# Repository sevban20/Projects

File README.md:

# Projects
It's about Sevban Kocael's projects. New projects will add.

## ARDUINO

### Fateining Farm Project
This is Arduino Nano-based project. It has 4 buttons to control menu operations. It can work in 2 modes: Automatic feed and cleaning bed of animals like cattle, sheep, etc., another mode is that manual feed and clean. It has 2 silos to store food. Every silo has its own motor that discharges food to the mixer. Mixer prepares food. After that, the conveyor starts feeding.
It has a cleaning unit to clean the ground. In addition, it has an RTC module to keep clock info. The RTC module is powered by a CR2032 battery. DHT22 sensor was used to measure humidity and temperature.To keep fresh air in the barn were used fans that control by temperature.The board has 2 power inputs, 5V, and 12V. 6 pieces of N-channel MOSFETs have been used to power the motors.

## ESP

### Home Automation Board
This is ESP8266 based project. It can control 4 pcs relays. Every relay also has an LED display to show work situations. To detect light density it has a photocell. To measure temperature and humidity to placed DHT22 sensor. It can power up to 5V-36V. The power unit of the board is based on LM2596S. It is going to connect the firebase real-time database so it can control by mobile application or any remote-controllable app.

## LED Dimmer
It is a led dimmer using LM555. There are one INPUT and one OUTPUT. It works with 12V. The brightness is adjustable with a 50K potentiometer. The maximum current is 3A.To control led used TO-220 package N channel MOSFET-IRFZ44N-.

## Web Scraping
### Get Jobs
This is a search job from timesjob.com. A user defines keyword and other options, the script search jobs from the website and shows all of them to the user. The input choices are Keyword, Number of pages, and location experience. If the user wants to save results, there is an option to save JSON format. <br />
Keyword(Required): Jobs keywords <br />
Number of Pages(Optional): How many pages will list <br />
Location(Optional): Job's location <br />
Experience(Optional): About Years <br />
### Get Last Topic
This script is working for that when the new topic opens the donanimhaber sicak firsatlar, the script gets the topic immediately. The user can see the last opened topic. If a day passed the topic's opened date the topic automatically will delete.

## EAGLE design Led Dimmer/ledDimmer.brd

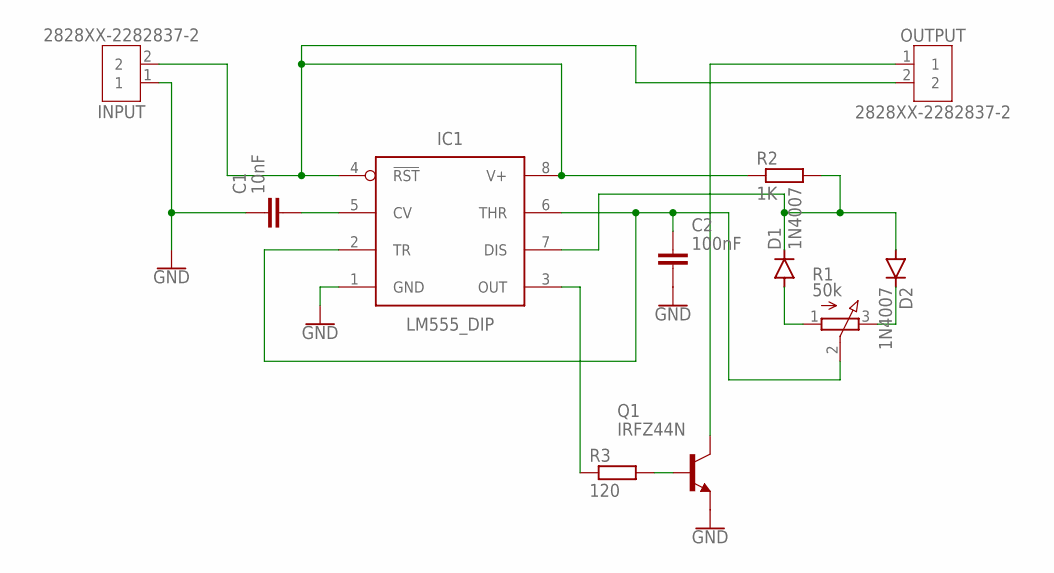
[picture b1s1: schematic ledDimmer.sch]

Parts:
C1: 10nF; CAPC1005X60
C2: 100nF; CAPC1005X60
D1, D2: 1N4007; DO-214AC
IC1: LM555_DIP; DIP826W53P254L959H508Q8B
INPUT: 2828XX-2282837-2; TERMBLK_508-2N
OUTPUT: 2828XX-2282837-2; TERMBLK_508-2N
Q1: IRFZ44N; TO220
R1: 50k; 3RP/1610N
R2: 1K; R0402
R3: 120; R0402

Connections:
GND: C1.1, C2.2, IC1.1 (GND), INPUT.1, Q1.3 (E)
unnamed: C1.2, IC1.5 (CV)
unnamed: D1.C, D2.A, IC1.7 (DIS), R2.2
unnamed: D1.A, R1.1 (A)
unnamed: D2.C, R1.3 (E)
unnamed: IC1.4 (!RST), IC1.8 (V+), INPUT.2, OUTPUT.2, R2.1
unnamed: OUTPUT.1, Q1.2 (C)
unnamed: C2.1, IC1.2 (TR), IC1.6 (THR), R1.2 (S)
unnamed: IC1.3 (OUT), R3.1
unnamed: Q1.1 (B), R3.2

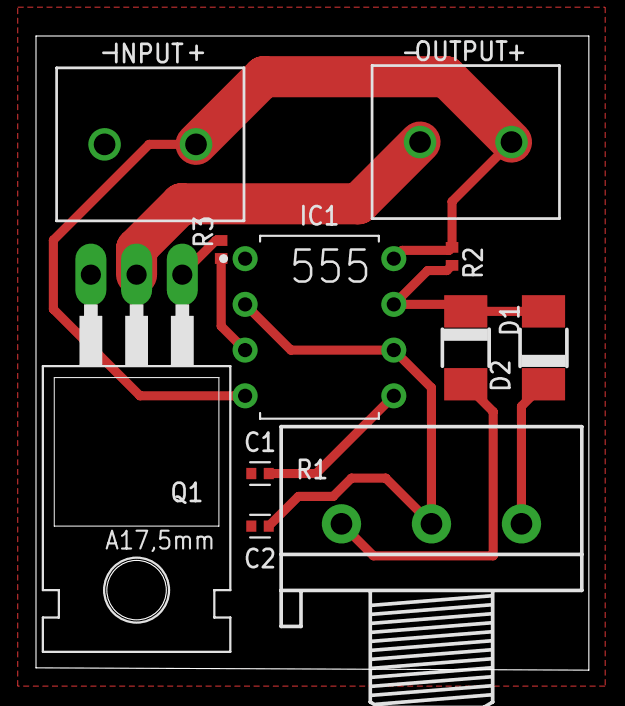
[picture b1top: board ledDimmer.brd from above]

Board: 2 copper layers, 30.7 x 35.2 mm, 11 parts (0 on the bottom side), 10 nets.

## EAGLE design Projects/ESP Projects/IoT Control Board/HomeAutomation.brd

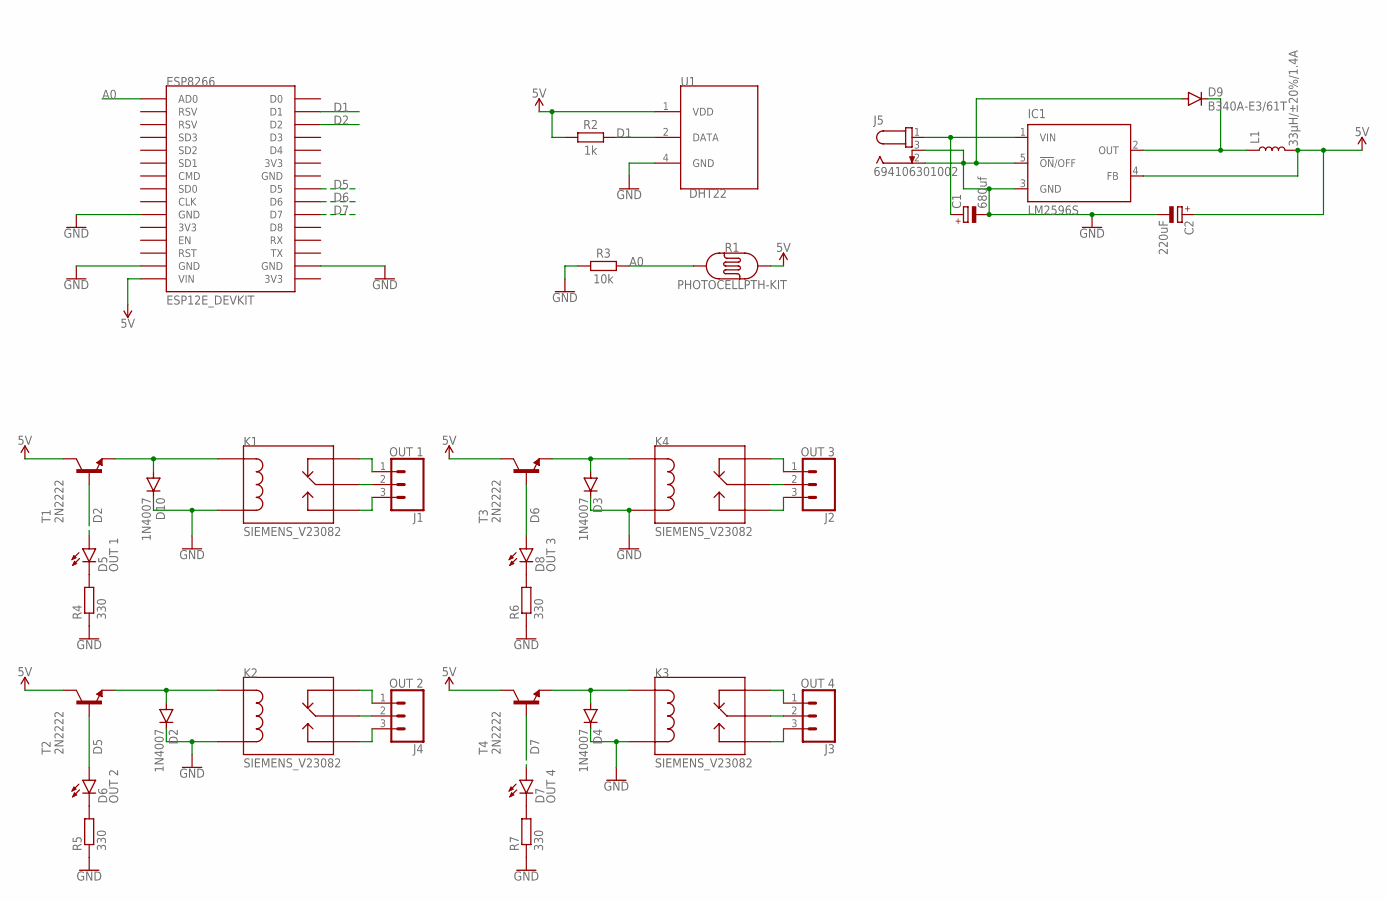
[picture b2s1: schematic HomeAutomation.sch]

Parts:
C1: 680uf; 153CLV-0405
C2: 220uF; 153CLV-0405
D2, D3, D4, D10: 1N4007; DO214AC
D5: OUT 1; CHIPLED_1206
D6: OUT 2; CHIPLED_1206
D7: OUT 4; CHIPLED_1206
D8: OUT 3; CHIPLED_1206
D9: B340A-E3/61T; DO214AC
ESP8266: ESP12E_DEVKIT
IC1: LM2596S; TO263-5
J1: OUT 1; SCREWTERMINAL-5MM-3
J2: OUT 3; SCREWTERMINAL-5MM-3
J3: OUT 4; SCREWTERMINAL-5MM-3
J4: OUT 2; SCREWTERMINAL-5MM-3
J5: 694106301002
K1, K2, K3, K4: SIEMENS_V23082; SIEMENS_V23082_RELAY
L1: 33µH/±20%/1.4A; SRN6045
R1: PHOTOCELLPTH-KIT; PHOTOCELL-KIT
R2: 1k; RESC1005X40
R3: 10k; RESC1005X40
R4, R5, R6, R7: 330; R0805
T1, T2, T3, T4: 2N2222; SOT23-BEC
U1: DHT22

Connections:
5V: C2.+, ESP8266.VIN, IC1.4 (FB), L1.2, R1.2, R2.1, T1.C, T2.C, T3.C, T4.C, U1.1 (VDD)
A0: ESP8266.AD0, R1.1, R3.2
D1: ESP8266.D1, R2.2, U1.2 (DATA)
D2: D5.A, ESP8266.D2, T1.B
D5: D6.A, ESP8266.D5, T2.B
D6: D8.A, ESP8266.D6, T3.B
D7: D7.A, ESP8266.D7, T4.B
GND: C1.-, C2.-, D2.C, D3.C, D4.C, D9.A, D10.C, ESP8266.GND@0 (GND), ESP8266.GND@1 (GND), ESP8266.GND@3 (GND), IC1.3 (GND), IC1.5 (!ON!/OFF), J5.2, J5.3, K1.P$2, K2.P$2, K3.P$2, K4.P$2, R3.1, R4.1, R5.1, R6.1, R7.1, U1.4 (GND)
unnamed: D10.A, K1.P$1, T1.E
unnamed: J2.1, K4.P$5
unnamed: D2.A, K2.P$1, T2.E
unnamed: J2.2, K4.P$3
unnamed: D3.A, K4.P$1, T3.E
unnamed: J2.3, K4.P$4
unnamed: J3.1, K3.P$5
unnamed: J3.2, K3.P$3
unnamed: J3.3, K3.P$4
unnamed: J4.1, K2.P$5
unnamed: J4.2, K2.P$3
unnamed: J4.3, K2.P$4
unnamed: J1.3, K1.P$4
unnamed: J1.2, K1.P$3
unnamed: J1.1, K1.P$5
unnamed: D5.C, R4.2
unnamed: D6.C, R5.2
unnamed: C1.+, IC1.1 (VIN), J5.1
unnamed: D8.C, R6.2
unnamed: D7.C, R7.2
unnamed: D9.C, IC1.2 (OUT), L1.1
unnamed: D4.A, K3.P$1, T4.E

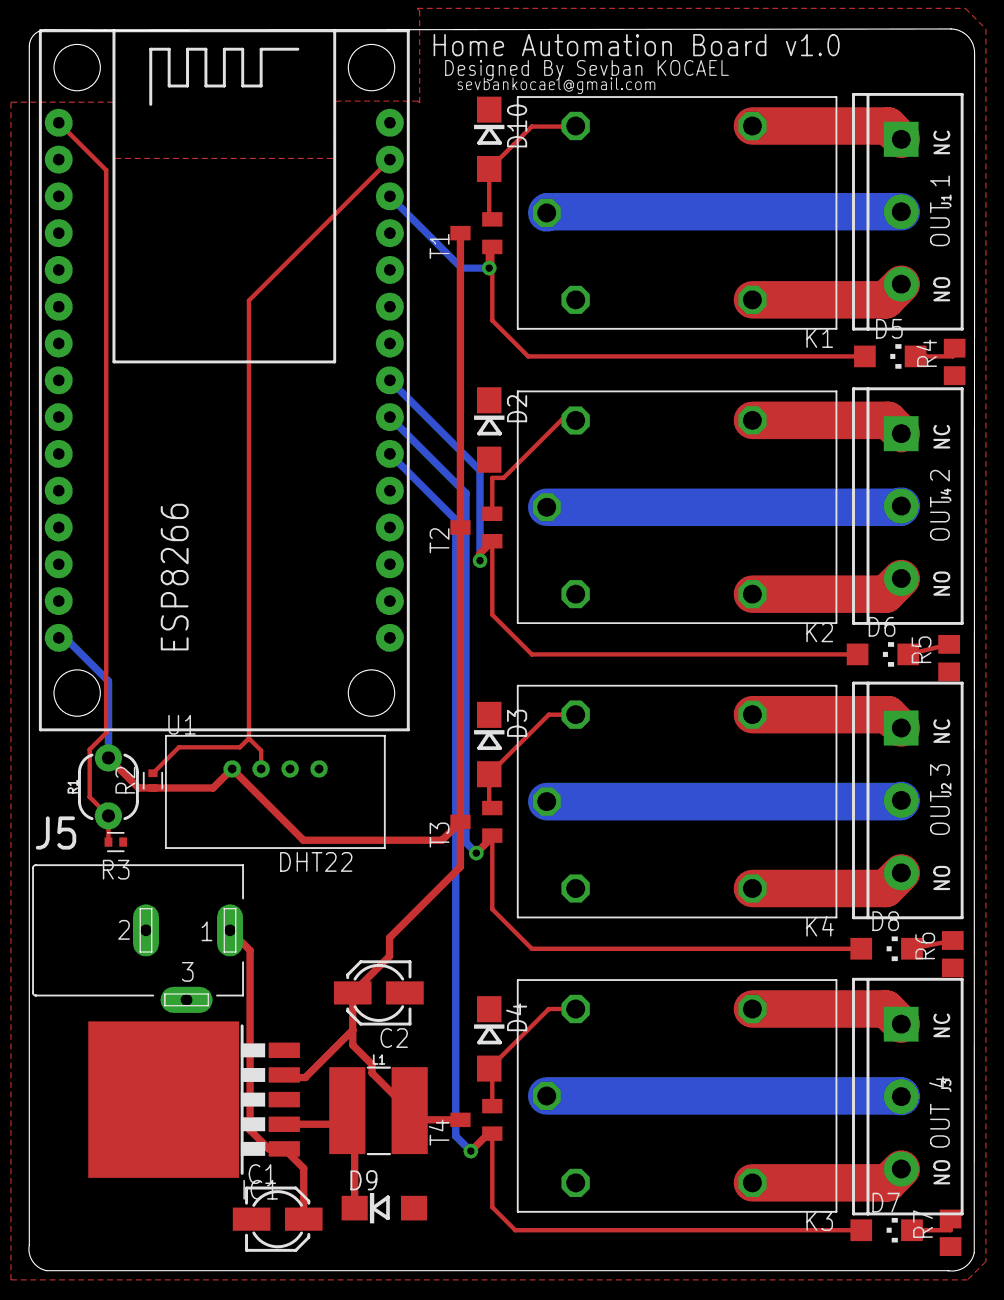
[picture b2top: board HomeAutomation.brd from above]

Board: 2 copper layers, 65.3 x 85.7 mm, 35 parts (0 on the bottom side), 30 nets.

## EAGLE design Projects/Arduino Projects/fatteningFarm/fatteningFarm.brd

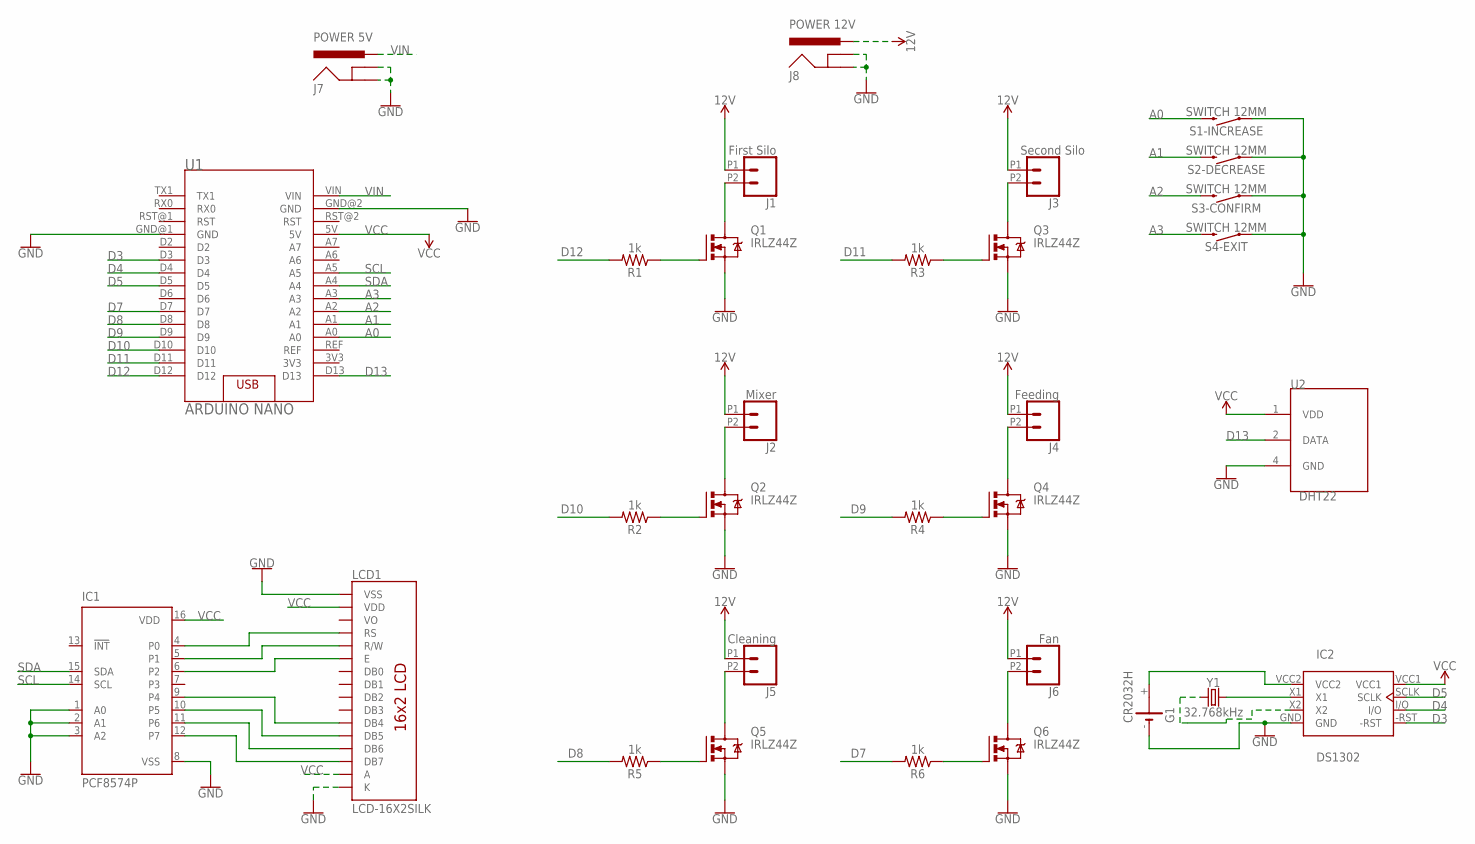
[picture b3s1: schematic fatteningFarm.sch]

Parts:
G1: CR2032H
IC1: PCF8574P; DIL16
IC2: DS1302; DIL08
J1: First Silo; 1X02_2.54_SCREWTERM
J2: Mixer; 1X02_2.54_SCREWTERM
J3: Second Silo; 1X02_2.54_SCREWTERM
J4: Feeding; 1X02_2.54_SCREWTERM
J5: Cleaning; 1X02_2.54_SCREWTERM
J6: Fan; 1X02_2.54_SCREWTERM
J7: POWER 5V; POWER_JACK_PTH
J8: POWER 12V; POWER_JACK_PTH
LCD1: LCD-16X2SILK; LCD-16X2
Q1, Q2, Q3, Q4, Q5, Q6: IRLZ44Z; TO220BH
R1, R2, R3, R4, R5, R6: 1k; AXIAL-0.3
S1-INCREASE, S2-DECREASE, S3-CONFIRM, S4-EXIT: SWITCH 12MM; TACTILE_SWITCH_PTH_12MM
U1: ARDUINO NANO; ARDUINO_NANO
U2: DHT22
Y1: 32.768kHz; CRYSTAL-PTH-2X6-CYL

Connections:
12V: J1.P1 (1), J2.P1 (1), J3.P1 (1), J4.P1 (1), J5.P1 (1), J6.P1 (1), J8.PWR
A0: S1-INCREASE.3 (2), U1.A0
A1: S2-DECREASE.3 (2), U1.A1
A2: S3-CONFIRM.3 (2), U1.A2
A3: S4-EXIT.3 (2), U1.A3
D3: IC2.-RST, U1.D3
D4: IC2.I/O, U1.D4
D5: IC2.SCLK, U1.D5
D7: R6.P$2 (2), U1.D7
D8: R5.P$2 (2), U1.D8
D9: R4.P$2 (2), U1.D9
D10: R2.P$2 (2), U1.D10
D11: R3.P$2 (2), U1.D11
D12: R1.P$2 (2), U1.D12
D13: U1.D13, U2.2 (DATA)
GND: G1.-, IC1.1 (A0), IC1.2 (A1), IC1.3 (A2), IC1.8 (VSS), IC2.GND, J7.GND, J7.GNDBREAK, J8.GND, J8.GNDBREAK, LCD1.1 (VSS), LCD1.16 (K), Q1.S, Q2.S, Q3.S, Q4.S, Q5.S, Q6.S, S1-INCREASE.1, S2-DECREASE.1, S3-CONFIRM.1, S4-EXIT.1, U1.GND@1 (GND), U1.GND@2 (GND), U2.4 (GND)
unnamed: IC2.X1, Y1.1
unnamed: Q1.G, R1.P$1 (1)
unnamed: J1.P2 (2), Q1.D
unnamed: IC1.4 (P0), LCD1.4 (RS)
unnamed: IC2.X2, Y1.2
unnamed: Q2.G, R2.P$1 (1)
unnamed: IC1.5 (P1), LCD1.5 (R/W)
unnamed: IC1.6 (P2), LCD1.6 (E)
unnamed: IC1.9 (P4), LCD1.11 (DB4)
unnamed: IC1.10 (P5), LCD1.12 (DB5)
unnamed: IC1.11 (P6), LCD1.13 (DB6)
unnamed: IC1.12 (P7), LCD1.14 (DB7)
unnamed: J2.P2 (2), Q2.D
unnamed: Q3.G, R3.P$1 (1)
unnamed: J3.P2 (2), Q3.D
unnamed: Q4.G, R4.P$1 (1)
unnamed: J4.P2 (2), Q4.D
unnamed: Q5.G, R5.P$1 (1)
unnamed: J5.P2 (2), Q5.D
unnamed: Q6.G, R6.P$1 (1)
unnamed: J6.P2 (2), Q6.D
SCL: IC1.14 (SCL), U1.A5
SDA: IC1.15 (SDA), U1.A4
VCC: IC1.16 (VDD), IC2.VCC1, LCD1.2 (VDD), LCD1.15 (A), U1.5V, U2.1 (VDD)
VCC2: G1.+, IC2.VCC2
VIN: J7.PWR, U1.VIN

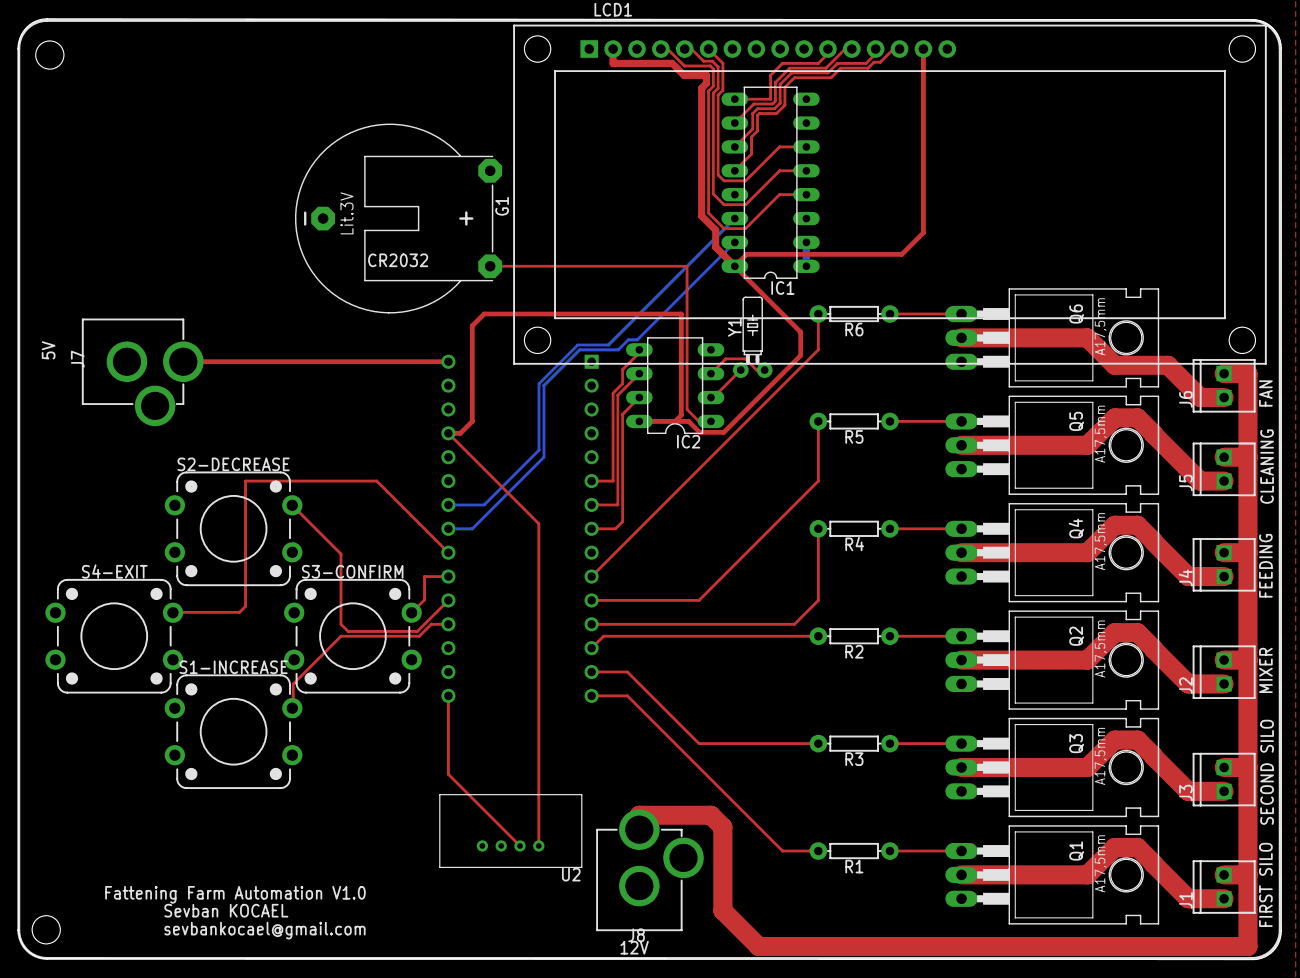
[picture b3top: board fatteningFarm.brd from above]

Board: 2 copper layers, 134.3 x 100.1 mm, 31 parts (1 on the bottom side), 42 nets.

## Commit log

2022-02-09 Update file path
2022-02-09 New Folder added
2022-02-09 Gerber file added
2022-02-10 web scrapping add
2022-02-10 compName add
2022-02-15 new files added
2022-02-15 update files
2022-02-15 readme file update

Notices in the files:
parts and their libraries:
SparkFun-PowerSymbols: Licensing: Creative Commons ShareAlike 4.0 International - https://creativecommons.org/licenses/by-sa/4.0
